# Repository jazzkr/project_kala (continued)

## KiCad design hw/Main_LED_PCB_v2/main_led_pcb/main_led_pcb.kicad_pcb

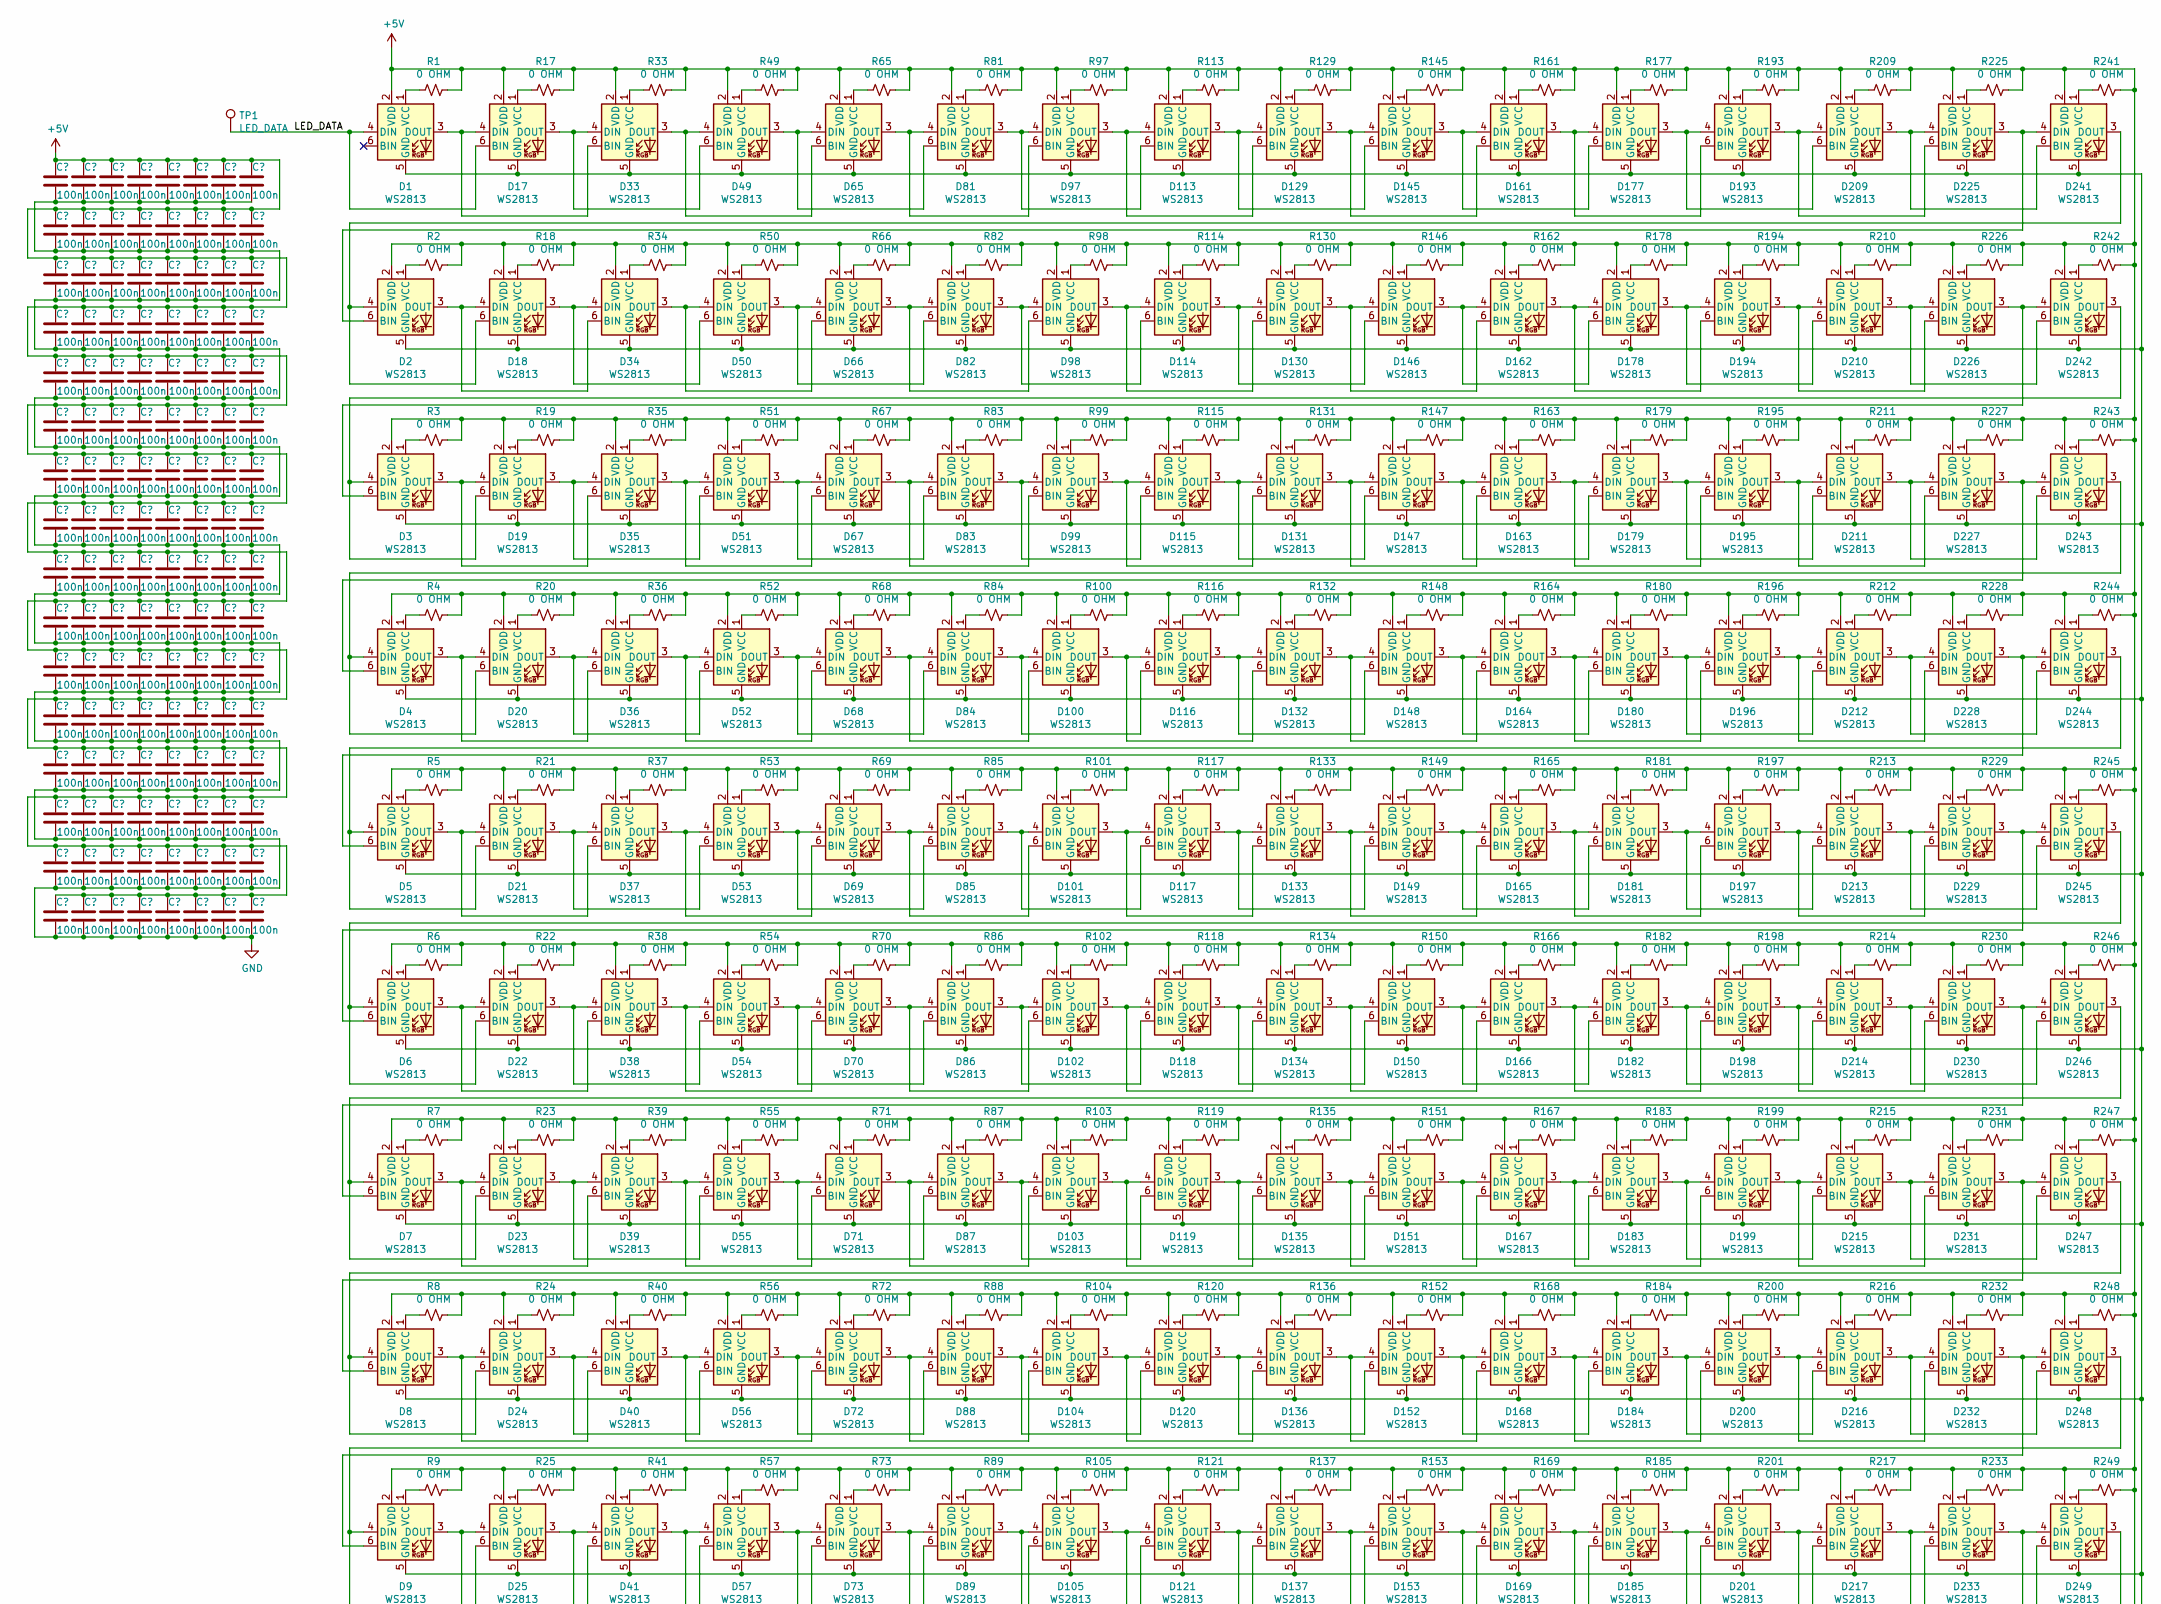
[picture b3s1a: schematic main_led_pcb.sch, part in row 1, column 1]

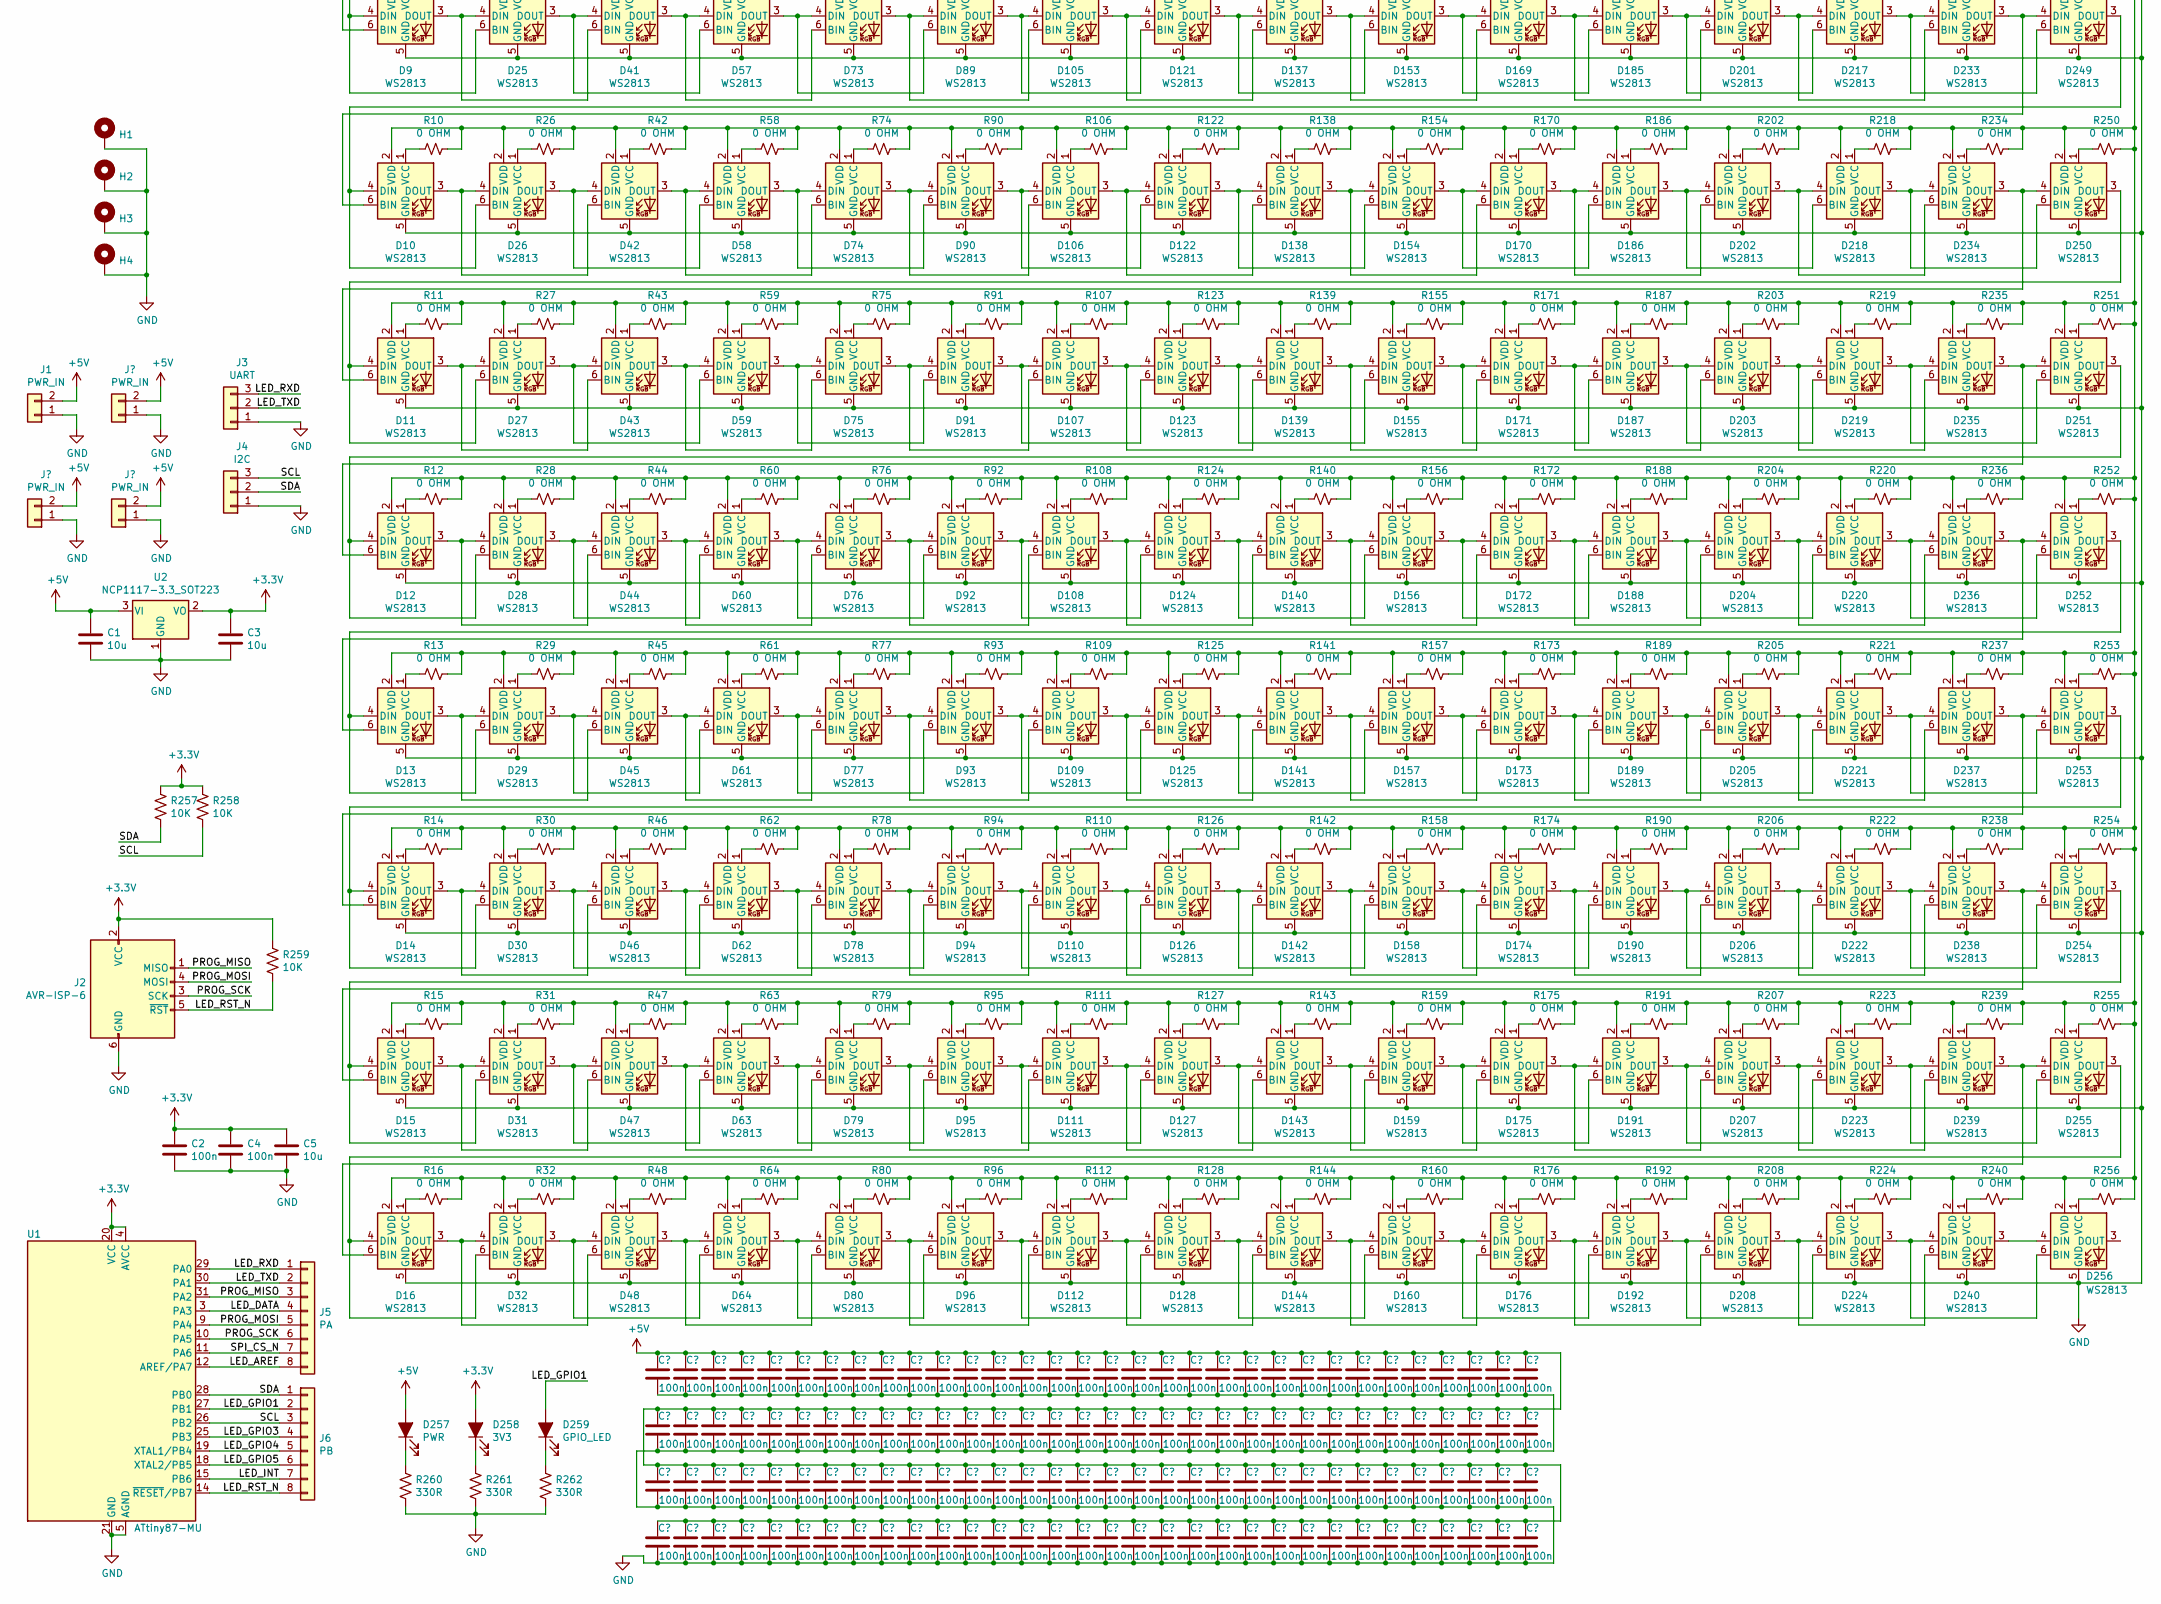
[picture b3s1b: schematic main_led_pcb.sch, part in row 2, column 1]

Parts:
C1, C3, C5: 10u; C_0805_2012Metric_Pad1.15x1.40mm_HandSolder
C2, C4: 100n; C_0805_2012Metric_Pad1.15x1.40mm_HandSolder
D1, D2, D3, D4, D5, D6, D7, D8, D9, D10, D11, D12, D13, D14, D15, D16, D17, D18, D19, D20, D21, D22, D23, D24, D25, D26, D27, D28, D29, D30, D31, D32, D33, D34, D35, D36, D37, D38, D39, D40, D41, D42, D43, D44, D45, D46, D47, D48, D49, D50, D51, D52, D53, D54, D55, D56, D57, D58, D59, D60, D61, D62, D63, D64, D65, D66, D67, D68, D69, D70, D71, D72, D73, D74, D75, D76, D77, D78, D79, D80, D81, D82, D83, D84, D85, D86, D87, D88, D89, D90, D91, D92, D93, D94, D95, D96, D97, D98, D99, D100, D101, D102, D103, D104, D105, D106, D107, D108, D109, D110, D111, D112, D113, D114, D115, D116, D117, D118, D119, D120, D121, D122, D123, D124, D125, D126, D127, D128, D129, D130, D131, D132, D133, D134, D135, D136, D137, D138, D139, D140, D141, D142, D143, D144, D145, D146, D147, D148, D149, D150, D151, D152, D153, D154, D155, D156, D157, D158, D159, D160, D161, D162, D163, D164, D165, D166, D167, D168, D169, D170, D171, D172, D173, D174, D175, D176, D177, D178, D179, D180, D181, D182, D183, D184, D185, D186, D187, D188, D189, D190, D191, D192, D193, D194, D195, D196, D197, D198, D199, D200, D201, D202, D203, D204, D205, D206, D207, D208, D209, D210, D211, D212, D213, D214, D215, D216, D217, D218, D219, D220, D221, D222, D223, D224, D225, D226, D227, D228, D229, D230, D231, D232, D233, D234, D235, D236, D237, D238, D239, D240, D241, D242, D243, D244, D245, D246, D247, D248, D249, D250, D251, D252, D253, D254, D255, D256: WS2813; LED_WS2812_PLCC6_5.0x5.0mm_P1.6mm
D257: PWR; LED_1206_3216Metric_Pad1.42x1.75mm_HandSolder
D258: 3V3; LED_1206_3216Metric_Pad1.42x1.75mm_HandSolder
D259: GPIO_LED; LED_1206_3216Metric_Pad1.42x1.75mm_HandSolder
H1: 1; MountingHole_2.2mm_M2_ISO7380_Pad
H2: 2; MountingHole_2.2mm_M2_ISO7380_Pad
H3: 3; MountingHole_2.2mm_M2_ISO7380_Pad
H4: 4; MountingHole_2.2mm_M2_ISO7380_Pad
J1: PWR_IN; PinHeader_1x02_P2.54mm_Vertical
J2: AVR-ISP-6; PinHeader_2x03_P2.54mm_Vertical_SMD
J3: UART; PinHeader_1x03_P2.54mm_Vertical
J4: I2C; PinHeader_1x03_P2.54mm_Vertical
J5: PA; PinHeader_1x08_P2.54mm_Vertical
J6: PB; PinHeader_1x08_P2.54mm_Vertical
R1, R2, R3, R4, R5, R6, R7, R8, R9, R10, R11, R12, R13, R14, R15, R16, R17, R18, R19, R20, R21, R22, R23, R24, R25, R26, R27, R28, R29, R30, R31, R32, R33, R34, R35, R36, R37, R38, R39, R40, R41, R42, R43, R44, R45, R46, R47, R48, R49, R50, R51, R52, R53, R54, R55, R56, R57, R58, R59, R60, R61, R62, R63, R64, R65, R66, R67, R68, R69, R70, R71, R72, R73, R74, R75, R76, R77, R78, R79, R80, R81, R82, R83, R84, R85, R86, R87, R88, R89, R90, R91, R92, R93, R94, R95, R96, R97, R98, R99, R100, R101, R102, R103, R104, R105, R106, R107, R108, R109, R110, R111, R112, R113, R114, R115, R116, R117, R118, R119, R120, R121, R122, R123, R124, R125, R126, R127, R128, R129, R130, R131, R132, R133, R134, R135, R136, R137, R138, R139, R140, R141, R142, R143, R144, R145, R146, R147, R148, R149, R150, R151, R152, R153, R154, R155, R156, R157, R158, R159, R160, R161, R162, R163, R164, R165, R166, R167, R168, R169, R170, R171, R172, R173, R174, R175, R176, R177, R178, R179, R180, R181, R182, R183, R184, R185, R186, R187, R188, R189, R190, R191, R192, R193, R194, R195, R196, R197, R198, R199, R200, R201, R202, R203, R204, R205, R206, R207, R208, R209, R210, R211, R212, R213, R214, R215, R216, R217, R218, R219, R220, R221, R222, R223, R224, R225, R226, R227, R228, R229, R230, R231, R232, R233, R234, R235, R236, R237, R238, R239, R240, R241, R242, R243, R244, R245, R246, R247, R248, R249, R250, R251, R252, R253, R254, R255, R256: 0 OHM; R_0805_2012Metric_Pad1.15x1.40mm_HandSolder
R257, R258, R259: 10K; R_0805_2012Metric_Pad1.15x1.40mm_HandSolder
R260, R261, R262: 330R; R_0805_2012Metric_Pad1.15x1.40mm_HandSolder
TP1: LED_DATA; TestPoint_Pad_D2.0mm
U1: ATtiny87-MU; QFN-32-1EP_5x5mm_P0.5mm_EP3.1x3.1mm
U2: NCP1117-3.3_SOT223; SOT-223-3_TabPin2

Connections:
+3V3: C2.1, C3.1, C4.1, C5.1, D258.2 (A), J2.2 (VCC), R257.1, R258.1, R259.1, U1.4 (AVCC), U1.20 (VCC), U2.2 (VO)
+5V: C1.1, D1.2 (VDD), D2.2 (VDD), D3.2 (VDD), D4.2 (VDD), D5.2 (VDD), D6.2 (VDD), D7.2 (VDD), D8.2 (VDD), D9.2 (VDD), D10.2 (VDD), D11.2 (VDD), D12.2 (VDD), D13.2 (VDD), D14.2 (VDD), D15.2 (VDD), D16.2 (VDD), D17.2 (VDD), D18.2 (VDD), D19.2 (VDD), D20.2 (VDD), D21.2 (VDD), D22.2 (VDD), D23.2 (VDD), D24.2 (VDD), D25.2 (VDD), D26.2 (VDD), D27.2 (VDD), D28.2 (VDD), D29.2 (VDD), D30.2 (VDD), D31.2 (VDD), D32.2 (VDD), D33.2 (VDD), D34.2 (VDD), D35.2 (VDD), D36.2 (VDD), D37.2 (VDD), D38.2 (VDD), D39.2 (VDD), D40.2 (VDD), D41.2 (VDD), D42.2 (VDD), D43.2 (VDD), D44.2 (VDD), D45.2 (VDD), D46.2 (VDD), D47.2 (VDD), D48.2 (VDD), D49.2 (VDD), D50.2 (VDD), D51.2 (VDD), D52.2 (VDD), D53.2 (VDD), D54.2 (VDD), D55.2 (VDD), D56.2 (VDD), D57.2 (VDD), D58.2 (VDD), D59.2 (VDD), D60.2 (VDD), D61.2 (VDD), D62.2 (VDD), D63.2 (VDD), D64.2 (VDD), D65.2 (VDD), D66.2 (VDD), D67.2 (VDD), D68.2 (VDD), D69.2 (VDD), D70.2 (VDD), D71.2 (VDD), D72.2 (VDD), D73.2 (VDD), D74.2 (VDD), D75.2 (VDD), D76.2 (VDD), D77.2 (VDD), D78.2 (VDD), D79.2 (VDD), D80.2 (VDD), D81.2 (VDD), D82.2 (VDD), D83.2 (VDD), D84.2 (VDD), D85.2 (VDD), D86.2 (VDD), D87.2 (VDD), D88.2 (VDD), D89.2 (VDD), D90.2 (VDD), D91.2 (VDD), D92.2 (VDD), D93.2 (VDD), D94.2 (VDD), D95.2 (VDD), D96.2 (VDD), D97.2 (VDD), D98.2 (VDD), D99.2 (VDD), D100.2 (VDD), D101.2 (VDD), D102.2 (VDD), D103.2 (VDD), D104.2 (VDD), D105.2 (VDD), D106.2 (VDD), D107.2 (VDD), D108.2 (VDD), D109.2 (VDD), D110.2 (VDD), D111.2 (VDD), D112.2 (VDD), D113.2 (VDD), D114.2 (VDD), D115.2 (VDD), D116.2 (VDD), D117.2 (VDD), D118.2 (VDD), D119.2 (VDD), D120.2 (VDD), D121.2 (VDD), D122.2 (VDD), D123.2 (VDD), D124.2 (VDD), D125.2 (VDD), D126.2 (VDD), D127.2 (VDD), D128.2 (VDD), D129.2 (VDD), D130.2 (VDD), D131.2 (VDD), D132.2 (VDD), D133.2 (VDD), D134.2 (VDD), D135.2 (VDD), D136.2 (VDD), D137.2 (VDD), D138.2 (VDD), D139.2 (VDD), D140.2 (VDD), D141.2 (VDD), D142.2 (VDD), D143.2 (VDD), D144.2 (VDD), D145.2 (VDD), D146.2 (VDD), D147.2 (VDD), D148.2 (VDD), D149.2 (VDD), D150.2 (VDD), D151.2 (VDD), D152.2 (VDD), D153.2 (VDD), D154.2 (VDD), D155.2 (VDD), D156.2 (VDD), D157.2 (VDD), D158.2 (VDD), D159.2 (VDD), D160.2 (VDD), D161.2 (VDD), D162.2 (VDD), D163.2 (VDD), D164.2 (VDD), D165.2 (VDD), D166.2 (VDD), D167.2 (VDD), D168.2 (VDD), D169.2 (VDD), D170.2 (VDD), D171.2 (VDD), D172.2 (VDD), D173.2 (VDD), D174.2 (VDD), D175.2 (VDD), D176.2 (VDD), D177.2 (VDD), D178.2 (VDD), D179.2 (VDD), D180.2 (VDD), D181.2 (VDD), D182.2 (VDD), D183.2 (VDD), D184.2 (VDD), D185.2 (VDD), D186.2 (VDD), D187.2 (VDD), D188.2 (VDD), D189.2 (VDD), D190.2 (VDD), D191.2 (VDD), D192.2 (VDD), D193.2 (VDD), D194.2 (VDD), D195.2 (VDD), D196.2 (VDD), D197.2 (VDD), D198.2 (VDD), D199.2 (VDD), D200.2 (VDD), D201.2 (VDD), D202.2 (VDD), D203.2 (VDD), D204.2 (VDD), D205.2 (VDD), D206.2 (VDD), D207.2 (VDD), D208.2 (VDD), D209.2 (VDD), D210.2 (VDD), D211.2 (VDD), D212.2 (VDD), D213.2 (VDD), D214.2 (VDD), D215.2 (VDD), D216.2 (VDD), D217.2 (VDD), D218.2 (VDD), D219.2 (VDD), D220.2 (VDD), D221.2 (VDD), D222.2 (VDD), D223.2 (VDD), D224.2 (VDD), D225.2 (VDD), D226.2 (VDD), D227.2 (VDD), D228.2 (VDD), D229.2 (VDD), D230.2 (VDD), D231.2 (VDD), D232.2 (VDD), D233.2 (VDD), D234.2 (VDD), D235.2 (VDD), D236.2 (VDD), D237.2 (VDD), D238.2 (VDD), D239.2 (VDD), D240.2 (VDD), D241.2 (VDD), D242.2 (VDD), D243.2 (VDD), D244.2 (VDD), D245.2 (VDD), D246.2 (VDD), D247.2 (VDD), D248.2 (VDD), D249.2 (VDD), D250.2 (VDD), D251.2 (VDD), D252.2 (VDD), D253.2 (VDD), D254.2 (VDD), D255.2 (VDD), D256.2 (VDD), D257.2 (A), J1.2, R1.1, R2.1, R3.1, R4.1, R5.1, R6.1, R7.1, R8.1, R9.1, R10.1, R11.1, R12.1, R13.1, R14.1, R15.1, R16.1, R17.1, R18.1, R19.1, R20.1, R21.1, R22.1, R23.1, R24.1, R25.1, R26.1, R27.1, R28.1, R29.1, R30.1, R31.1, R32.1, R33.1, R34.1, R35.1, R36.1, R37.1, R38.1, R39.1, R40.1, R41.1, R42.1, R43.1, R44.1, R45.1, R46.1, R47.1, R48.1, R49.1, R50.1, R51.1, R52.1, R53.1, R54.1, R55.1, R56.1, R57.1, R58.1, R59.1, R60.1, R61.1, R62.1, R63.1, R64.1, R65.1, R66.1, R67.1, R68.1, R69.1, R70.1, R71.1, R72.1, R73.1, R74.1, R75.1, R76.1, R77.1, R78.1, R79.1, R80.1, R81.1, R82.1, R83.1, R84.1, R85.1, R86.1, R87.1, R88.1, R89.1, R90.1, R91.1, R92.1, R93.1, R94.1, R95.1, R96.1, R97.1, R98.1, R99.1, R100.1, R101.1, R102.1, R103.1, R104.1, R105.1, R106.1, R107.1, R108.1, R109.1, R110.1, R111.1, R112.1, R113.1, R114.1, R115.1, R116.1, R117.1, R118.1, R119.1, R120.1, R121.1, R122.1, R123.1, R124.1, R125.1, R126.1, R127.1, R128.1, R129.1, R130.1, R131.1, R132.1, R133.1, R134.1, R135.1, R136.1, R137.1, R138.1, R139.1, R140.1, R141.1, R142.1, R143.1, R144.1, R145.1, R146.1, R147.1, R148.1, R149.1, R150.1, R151.1, R152.1, R153.1, R154.1, R155.1, R156.1, R157.1, R158.1, R159.1, R160.1, R161.1, R162.1, R163.1, R164.1, R165.1, R166.1, R167.1, R168.1, R169.1, R170.1, R171.1, R172.1, R173.1, R174.1, R175.1, R176.1, R177.1, R178.1, R179.1, R180.1, R181.1, R182.1, R183.1, R184.1, R185.1, R186.1, R187.1, R188.1, R189.1, R190.1, R191.1, R192.1, R193.1, R194.1, R195.1, R196.1, R197.1, R198.1, R199.1, R200.1, R201.1, R202.1, R203.1, R204.1, R205.1, R206.1, R207.1, R208.1, R209.1, R210.1, R211.1, R212.1, R213.1, R214.1, R215.1, R216.1, R217.1, R218.1, R219.1, R220.1, R221.1, R222.1, R223.1, R224.1, R225.1, R226.1, R227.1, R228.1, R229.1, R230.1, R231.1, R232.1, R233.1, R234.1, R235.1, R236.1, R237.1, R238.1, R239.1, R240.1, R241.1, R242.1, R243.1, R244.1, R245.1, R246.1, R247.1, R248.1, R249.1, R250.1, R251.1, R252.1, R253.1, R254.1, R255.1, R256.1, U2.3 (VI)
/LED_AREF: J5.8, U1.12 (AREF/PA7)
/LED_DATA: D1.4 (DIN), D17.6 (BIN), J5.4, TP1.1, U1.3 (PA3)
/LED_GPIO1: D259.2 (A), J6.2, U1.27 (PB1)
/LED_GPIO3: J6.4, U1.25 (PB3)
/LED_GPIO4: J6.5, U1.19 (XTAL1/PB4)
/LED_GPIO5: J6.6, U1.18 (XTAL2/PB5)
/LED_INT: J6.7, U1.15 (PB6)
/LED_RST_N: J2.5 (~RST), J6.8, R259.2, U1.14 (~RESET~/PB7)
/PROG_MISO: J2.1 (MISO), J5.3, U1.31 (PA2)
/PROG_MOSI: J2.4 (MOSI), J5.5, U1.9 (PA4)
/PROG_SCK: J2.3 (SCK), J5.6, U1.10 (PA5)
/SPI_CS_N: J5.7, U1.11 (PA6)
unnamed: D1.1 (VCC), R1.2
unnamed: D1.3 (DOUT), D17.4 (DIN), D33.6 (BIN)
unnamed: D2.1 (VCC), R2.2
unnamed: D2.6 (BIN), D225.3 (DOUT), D241.4 (DIN)
unnamed: D3.1 (VCC), R3.2
unnamed: D4.1 (VCC), R4.2
unnamed: D5.1 (VCC), R5.2
unnamed: D6.1 (VCC), R6.2
unnamed: D7.1 (VCC), R7.2
unnamed: D8.1 (VCC), R8.2
unnamed: D9.1 (VCC), R9.2
unnamed: D10.1 (VCC), R10.2
unnamed: D10.3 (DOUT), D26.4 (DIN), D42.6 (BIN)
unnamed: D10.4 (DIN), D26.6 (BIN), D249.3 (DOUT)
unnamed: D10.6 (BIN), D233.3 (DOUT), D249.4 (DIN)
unnamed: D11.1 (VCC), R11.2
unnamed: D11.3 (DOUT), D27.4 (DIN), D43.6 (BIN)
unnamed: D11.4 (DIN), D27.6 (BIN), D250.3 (DOUT)
unnamed: D11.6 (BIN), D234.3 (DOUT), D250.4 (DIN)
unnamed: D12.1 (VCC), R12.2
unnamed: D12.3 (DOUT), D28.4 (DIN), D44.6 (BIN)
unnamed: D12.4 (DIN), D28.6 (BIN), D251.3 (DOUT)
unnamed: D12.6 (BIN), D235.3 (DOUT), D251.4 (DIN)
unnamed: D13.1 (VCC), R13.2
unnamed: D13.3 (DOUT), D29.4 (DIN), D45.6 (BIN)
unnamed: D13.4 (DIN), D29.6 (BIN), D252.3 (DOUT)
unnamed: D13.6 (BIN), D236.3 (DOUT), D252.4 (DIN)
unnamed: D14.1 (VCC), R14.2
unnamed: D14.3 (DOUT), D30.4 (DIN), D46.6 (BIN)
unnamed: D14.4 (DIN), D30.6 (BIN), D253.3 (DOUT)
unnamed: D14.6 (BIN), D237.3 (DOUT), D253.4 (DIN)
unnamed: D15.1 (VCC), R15.2
unnamed: D15.3 (DOUT), D31.4 (DIN), D47.6 (BIN)
unnamed: D15.4 (DIN), D31.6 (BIN), D254.3 (DOUT)
unnamed: D15.6 (BIN), D238.3 (DOUT), D254.4 (DIN)
unnamed: D16.1 (VCC), R16.2
unnamed: D16.3 (DOUT), D32.4 (DIN), D48.6 (BIN)
unnamed: D16.4 (DIN), D32.6 (BIN), D255.3 (DOUT)
unnamed: D16.6 (BIN), D239.3 (DOUT), D255.4 (DIN)
unnamed: D17.1 (VCC), R17.2
unnamed: D17.3 (DOUT), D33.4 (DIN), D49.6 (BIN)
unnamed: D18.1 (VCC), R18.2
unnamed: D18.3 (DOUT), D34.4 (DIN), D50.6 (BIN)
unnamed: D2.3 (DOUT), D18.4 (DIN), D34.6 (BIN)
unnamed: D2.4 (DIN), D18.6 (BIN), D241.3 (DOUT)
unnamed: D19.1 (VCC), R19.2
unnamed: D19.3 (DOUT), D35.4 (DIN), D51.6 (BIN)
unnamed: D3.3 (DOUT), D19.4 (DIN), D35.6 (BIN)
unnamed: D3.4 (DIN), D19.6 (BIN), D242.3 (DOUT)
unnamed: D20.1 (VCC), R20.2
unnamed: D20.3 (DOUT), D36.4 (DIN), D52.6 (BIN)
unnamed: D4.3 (DOUT), D20.4 (DIN), D36.6 (BIN)
unnamed: D4.4 (DIN), D20.6 (BIN), D243.3 (DOUT)
unnamed: D21.1 (VCC), R21.2
unnamed: D21.3 (DOUT), D37.4 (DIN), D53.6 (BIN)
unnamed: D5.3 (DOUT), D21.4 (DIN), D37.6 (BIN)
unnamed: D5.4 (DIN), D21.6 (BIN), D244.3 (DOUT)
unnamed: D22.1 (VCC), R22.2
unnamed: D22.3 (DOUT), D38.4 (DIN), D54.6 (BIN)
unnamed: D6.3 (DOUT), D22.4 (DIN), D38.6 (BIN)
unnamed: D6.4 (DIN), D22.6 (BIN), D245.3 (DOUT)
unnamed: D23.1 (VCC), R23.2
unnamed: D23.3 (DOUT), D39.4 (DIN), D55.6 (BIN)
unnamed: D7.3 (DOUT), D23.4 (DIN), D39.6 (BIN)
unnamed: D7.4 (DIN), D23.6 (BIN), D246.3 (DOUT)
unnamed: D24.1 (VCC), R24.2
unnamed: D24.3 (DOUT), D40.4 (DIN), D56.6 (BIN)
unnamed: D8.3 (DOUT), D24.4 (DIN), D40.6 (BIN)
unnamed: D8.4 (DIN), D24.6 (BIN), D247.3 (DOUT)
unnamed: D25.1 (VCC), R25.2
unnamed: D25.3 (DOUT), D41.4 (DIN), D57.6 (BIN)
unnamed: D9.3 (DOUT), D25.4 (DIN), D41.6 (BIN)
unnamed: D26.1 (VCC), R26.2
unnamed: D26.3 (DOUT), D42.4 (DIN), D58.6 (BIN)
unnamed: D27.1 (VCC), R27.2
unnamed: D27.3 (DOUT), D43.4 (DIN), D59.6 (BIN)
unnamed: D28.1 (VCC), R28.2
unnamed: D28.3 (DOUT), D44.4 (DIN), D60.6 (BIN)
unnamed: D29.1 (VCC), R29.2
unnamed: D29.3 (DOUT), D45.4 (DIN), D61.6 (BIN)
unnamed: D30.1 (VCC), R30.2
unnamed: D30.3 (DOUT), D46.4 (DIN), D62.6 (BIN)
unnamed: D31.1 (VCC), R31.2
unnamed: D31.3 (DOUT), D47.4 (DIN), D63.6 (BIN)
unnamed: D32.1 (VCC), R32.2
unnamed: D32.3 (DOUT), D48.4 (DIN), D64.6 (BIN)
unnamed: D33.1 (VCC), R33.2
unnamed: D33.3 (DOUT), D49.4 (DIN), D65.6 (BIN)
unnamed: D34.1 (VCC), R34.2
unnamed: D34.3 (DOUT), D50.4 (DIN), D66.6 (BIN)
unnamed: D35.1 (VCC), R35.2
unnamed: D35.3 (DOUT), D51.4 (DIN), D67.6 (BIN)
unnamed: D36.1 (VCC), R36.2
unnamed: D36.3 (DOUT), D52.4 (DIN), D68.6 (BIN)
unnamed: D37.1 (VCC), R37.2
unnamed: D37.3 (DOUT), D53.4 (DIN), D69.6 (BIN)
unnamed: D38.1 (VCC), R38.2
unnamed: D38.3 (DOUT), D54.4 (DIN), D70.6 (BIN)
unnamed: D39.1 (VCC), R39.2
unnamed: D39.3 (DOUT), D55.4 (DIN), D71.6 (BIN)
unnamed: D40.1 (VCC), R40.2
unnamed: D40.3 (DOUT), D56.4 (DIN), D72.6 (BIN)
unnamed: D41.1 (VCC), R41.2
unnamed: D41.3 (DOUT), D57.4 (DIN), D73.6 (BIN)
unnamed: D42.1 (VCC), R42.2
unnamed: D42.3 (DOUT), D58.4 (DIN), D74.6 (BIN)
unnamed: D43.1 (VCC), R43.2
unnamed: D43.3 (DOUT), D59.4 (DIN), D75.6 (BIN)
unnamed: D44.1 (VCC), R44.2
unnamed: D44.3 (DOUT), D60.4 (DIN), D76.6 (BIN)
unnamed: D45.1 (VCC), R45.2
unnamed: D45.3 (DOUT), D61.4 (DIN), D77.6 (BIN)
unnamed: D46.1 (VCC), R46.2
unnamed: D46.3 (DOUT), D62.4 (DIN), D78.6 (BIN)
unnamed: D47.1 (VCC), R47.2
unnamed: D47.3 (DOUT), D63.4 (DIN), D79.6 (BIN)
unnamed: D48.1 (VCC), R48.2
unnamed: D48.3 (DOUT), D64.4 (DIN), D80.6 (BIN)
unnamed: D49.1 (VCC), R49.2
unnamed: D49.3 (DOUT), D65.4 (DIN), D81.6 (BIN)
unnamed: D50.1 (VCC), R50.2
unnamed: D50.3 (DOUT), D66.4 (DIN), D82.6 (BIN)
unnamed: D51.1 (VCC), R51.2
unnamed: D51.3 (DOUT), D67.4 (DIN), D83.6 (BIN)
unnamed: D52.1 (VCC), R52.2
unnamed: D52.3 (DOUT), D68.4 (DIN), D84.6 (BIN)
unnamed: D53.1 (VCC), R53.2
unnamed: D53.3 (DOUT), D69.4 (DIN), D85.6 (BIN)
unnamed: D54.1 (VCC), R54.2
unnamed: D54.3 (DOUT), D70.4 (DIN), D86.6 (BIN)
unnamed: D55.1 (VCC), R55.2
unnamed: D55.3 (DOUT), D71.4 (DIN), D87.6 (BIN)
unnamed: D56.1 (VCC), R56.2
unnamed: D56.3 (DOUT), D72.4 (DIN), D88.6 (BIN)
unnamed: D57.1 (VCC), R57.2
unnamed: D57.3 (DOUT), D73.4 (DIN), D89.6 (BIN)
unnamed: D58.1 (VCC), R58.2
unnamed: D58.3 (DOUT), D74.4 (DIN), D90.6 (BIN)
unnamed: D59.1 (VCC), R59.2
unnamed: D59.3 (DOUT), D75.4 (DIN), D91.6 (BIN)
unnamed: D60.1 (VCC), R60.2
unnamed: D60.3 (DOUT), D76.4 (DIN), D92.6 (BIN)
unnamed: D61.1 (VCC), R61.2
unnamed: D61.3 (DOUT), D77.4 (DIN), D93.6 (BIN)
unnamed: D62.1 (VCC), R62.2
unnamed: D62.3 (DOUT), D78.4 (DIN), D94.6 (BIN)
unnamed: D63.1 (VCC), R63.2
unnamed: D63.3 (DOUT), D79.4 (DIN), D95.6 (BIN)
unnamed: D64.1 (VCC), R64.2
unnamed: D64.3 (DOUT), D80.4 (DIN), D96.6 (BIN)
unnamed: D65.1 (VCC), R65.2
unnamed: D65.3 (DOUT), D81.4 (DIN), D97.6 (BIN)
unnamed: D66.1 (VCC), R66.2
unnamed: D66.3 (DOUT), D82.4 (DIN), D98.6 (BIN)
unnamed: D67.1 (VCC), R67.2
unnamed: D67.3 (DOUT), D83.4 (DIN), D99.6 (BIN)
unnamed: D68.1 (VCC), R68.2
unnamed: D69.1 (VCC), R69.2
unnamed: D70.1 (VCC), R70.2
unnamed: D71.1 (VCC), R71.2
unnamed: D72.1 (VCC), R72.2
unnamed: D73.1 (VCC), R73.2
unnamed: D74.1 (VCC), R74.2
unnamed: D75.1 (VCC), R75.2
unnamed: D76.1 (VCC), R76.2
unnamed: D77.1 (VCC), R77.2
unnamed: D78.1 (VCC), R78.2
unnamed: D79.1 (VCC), R79.2
unnamed: D80.1 (VCC), R80.2
unnamed: D81.1 (VCC), R81.2
unnamed: D82.1 (VCC), R82.2
unnamed: D83.1 (VCC), R83.2
unnamed: D84.1 (VCC), R84.2
unnamed: D85.1 (VCC), R85.2
unnamed: D86.1 (VCC), R86.2
unnamed: D87.1 (VCC), R87.2
unnamed: D88.1 (VCC), R88.2
unnamed: D89.1 (VCC), R89.2
unnamed: D90.1 (VCC), R90.2
unnamed: D91.1 (VCC), R91.2
unnamed: D92.1 (VCC), R92.2
unnamed: D93.1 (VCC), R93.2
unnamed: D94.1 (VCC), R94.2
unnamed: D95.1 (VCC), R95.2
unnamed: D96.1 (VCC), R96.2
unnamed: D97.1 (VCC), R97.2
unnamed: D98.1 (VCC), R98.2
unnamed: D99.1 (VCC), R99.2
unnamed: D100.1 (VCC), R100.2
unnamed: D100.3 (DOUT), D116.4 (DIN), D132.6 (BIN)
unnamed: D84.3 (DOUT), D100.4 (DIN), D116.6 (BIN)
unnamed: D68.3 (DOUT), D84.4 (DIN), D100.6 (BIN)
unnamed: D101.1 (VCC), R101.2
unnamed: D101.3 (DOUT), D117.4 (DIN), D133.6 (BIN)
unnamed: D85.3 (DOUT), D101.4 (DIN), D117.6 (BIN)
unnamed: D69.3 (DOUT), D85.4 (DIN), D101.6 (BIN)
unnamed: D102.1 (VCC), R102.2
unnamed: D102.3 (DOUT), D118.4 (DIN), D134.6 (BIN)
unnamed: D86.3 (DOUT), D102.4 (DIN), D118.6 (BIN)
unnamed: D70.3 (DOUT), D86.4 (DIN), D102.6 (BIN)
unnamed: D103.1 (VCC), R103.2
unnamed: D103.3 (DOUT), D119.4 (DIN), D135.6 (BIN)
unnamed: D87.3 (DOUT), D103.4 (DIN), D119.6 (BIN)
unnamed: D71.3 (DOUT), D87.4 (DIN), D103.6 (BIN)
unnamed: D104.1 (VCC), R104.2
unnamed: D104.3 (DOUT), D120.4 (DIN), D136.6 (BIN)
unnamed: D88.3 (DOUT), D104.4 (DIN), D120.6 (BIN)
unnamed: D72.3 (DOUT), D88.4 (DIN), D104.6 (BIN)
unnamed: D105.1 (VCC), R105.2
unnamed: D105.3 (DOUT), D121.4 (DIN), D137.6 (BIN)
unnamed: D89.3 (DOUT), D105.4 (DIN), D121.6 (BIN)
unnamed: D73.3 (DOUT), D89.4 (DIN), D105.6 (BIN)
unnamed: D106.1 (VCC), R106.2
unnamed: D106.3 (DOUT), D122.4 (DIN), D138.6 (BIN)
unnamed: D90.3 (DOUT), D106.4 (DIN), D122.6 (BIN)
unnamed: D74.3 (DOUT), D90.4 (DIN), D106.6 (BIN)
unnamed: D107.1 (VCC), R107.2
unnamed: D107.3 (DOUT), D123.4 (DIN), D139.6 (BIN)
unnamed: D91.3 (DOUT), D107.4 (DIN), D123.6 (BIN)
unnamed: D75.3 (DOUT), D91.4 (DIN), D107.6 (BIN)
unnamed: D108.1 (VCC), R108.2
unnamed: D108.3 (DOUT), D124.4 (DIN), D140.6 (BIN)
unnamed: D92.3 (DOUT), D108.4 (DIN), D124.6 (BIN)
unnamed: D76.3 (DOUT), D92.4 (DIN), D108.6 (BIN)
unnamed: D109.1 (VCC), R109.2
unnamed: D109.3 (DOUT), D125.4 (DIN), D141.6 (BIN)
unnamed: D93.3 (DOUT), D109.4 (DIN), D125.6 (BIN)
unnamed: D77.3 (DOUT), D93.4 (DIN), D109.6 (BIN)
unnamed: D110.1 (VCC), R110.2
unnamed: D110.3 (DOUT), D126.4 (DIN), D142.6 (BIN)
unnamed: D94.3 (DOUT), D110.4 (DIN), D126.6 (BIN)
unnamed: D78.3 (DOUT), D94.4 (DIN), D110.6 (BIN)
unnamed: D111.1 (VCC), R111.2
unnamed: D111.3 (DOUT), D127.4 (DIN), D143.6 (BIN)
unnamed: D95.3 (DOUT), D111.4 (DIN), D127.6 (BIN)
unnamed: D79.3 (DOUT), D95.4 (DIN), D111.6 (BIN)
unnamed: D112.1 (VCC), R112.2
unnamed: D112.3 (DOUT), D128.4 (DIN), D144.6 (BIN)
unnamed: D96.3 (DOUT), D112.4 (DIN), D128.6 (BIN)
unnamed: D80.3 (DOUT), D96.4 (DIN), D112.6 (BIN)
unnamed: D113.1 (VCC), R113.2
unnamed: D113.3 (DOUT), D129.4 (DIN), D145.6 (BIN)
unnamed: D97.3 (DOUT), D113.4 (DIN), D129.6 (BIN)
unnamed: D81.3 (DOUT), D97.4 (DIN), D113.6 (BIN)
unnamed: D114.1 (VCC), R114.2
unnamed: D114.3 (DOUT), D130.4 (DIN), D146.6 (BIN)
unnamed: D98.3 (DOUT), D114.4 (DIN), D130.6 (BIN)
unnamed: D82.3 (DOUT), D98.4 (DIN), D114.6 (BIN)
unnamed: D115.1 (VCC), R115.2
unnamed: D115.3 (DOUT), D131.4 (DIN), D147.6 (BIN)
unnamed: D99.3 (DOUT), D115.4 (DIN), D131.6 (BIN)
unnamed: D83.3 (DOUT), D99.4 (DIN), D115.6 (BIN)
unnamed: D116.1 (VCC), R116.2
unnamed: D116.3 (DOUT), D132.4 (DIN), D148.6 (BIN)
unnamed: D117.1 (VCC), R117.2
unnamed: D117.3 (DOUT), D133.4 (DIN), D149.6 (BIN)
unnamed: D118.1 (VCC), R118.2
unnamed: D118.3 (DOUT), D134.4 (DIN), D150.6 (BIN)
unnamed: D119.1 (VCC), R119.2
unnamed: D119.3 (DOUT), D135.4 (DIN), D151.6 (BIN)
unnamed: D120.1 (VCC), R120.2
unnamed: D120.3 (DOUT), D136.4 (DIN), D152.6 (BIN)
unnamed: D121.1 (VCC), R121.2
unnamed: D121.3 (DOUT), D137.4 (DIN), D153.6 (BIN)
unnamed: D122.1 (VCC), R122.2
unnamed: D122.3 (DOUT), D138.4 (DIN), D154.6 (BIN)
unnamed: D123.1 (VCC), R123.2
unnamed: D123.3 (DOUT), D139.4 (DIN), D155.6 (BIN)
unnamed: D124.1 (VCC), R124.2
unnamed: D124.3 (DOUT), D140.4 (DIN), D156.6 (BIN)
unnamed: D125.1 (VCC), R125.2
unnamed: D125.3 (DOUT), D141.4 (DIN), D157.6 (BIN)
unnamed: D126.1 (VCC), R126.2
unnamed: D126.3 (DOUT), D142.4 (DIN), D158.6 (BIN)
unnamed: D127.1 (VCC), R127.2
unnamed: D127.3 (DOUT), D143.4 (DIN), D159.6 (BIN)
unnamed: D128.1 (VCC), R128.2
unnamed: D128.3 (DOUT), D144.4 (DIN), D160.6 (BIN)
unnamed: D129.1 (VCC), R129.2
unnamed: D129.3 (DOUT), D145.4 (DIN), D161.6 (BIN)
unnamed: D130.1 (VCC), R130.2
unnamed: D130.3 (DOUT), D146.4 (DIN), D162.6 (BIN)
unnamed: D131.1 (VCC), R131.2
unnamed: D131.3 (DOUT), D147.4 (DIN), D163.6 (BIN)
unnamed: D132.1 (VCC), R132.2
unnamed: D132.3 (DOUT), D148.4 (DIN), D164.6 (BIN)
unnamed: D133.1 (VCC), R133.2
unnamed: D133.3 (DOUT), D149.4 (DIN), D165.6 (BIN)
unnamed: D134.1 (VCC), R134.2
unnamed: D134.3 (DOUT), D150.4 (DIN), D166.6 (BIN)
unnamed: D135.1 (VCC), R135.2
unnamed: D135.3 (DOUT), D151.4 (DIN), D167.6 (BIN)
unnamed: D136.1 (VCC), R136.2
unnamed: D136.3 (DOUT), D152.4 (DIN), D168.6 (BIN)
unnamed: D137.1 (VCC), R137.2
unnamed: D137.3 (DOUT), D153.4 (DIN), D169.6 (BIN)
unnamed: D138.1 (VCC), R138.2
unnamed: D138.3 (DOUT), D154.4 (DIN), D170.6 (BIN)
unnamed: D139.1 (VCC), R139.2
unnamed: D139.3 (DOUT), D155.4 (DIN), D171.6 (BIN)
unnamed: D140.1 (VCC), R140.2
unnamed: D140.3 (DOUT), D156.4 (DIN), D172.6 (BIN)
unnamed: D141.1 (VCC), R141.2
unnamed: D141.3 (DOUT), D157.4 (DIN), D173.6 (BIN)
unnamed: D142.1 (VCC), R142.2
unnamed: D142.3 (DOUT), D158.4 (DIN), D174.6 (BIN)
unnamed: D143.1 (VCC), R143.2
unnamed: D143.3 (DOUT), D159.4 (DIN), D175.6 (BIN)
unnamed: D144.1 (VCC), R144.2
unnamed: D144.3 (DOUT), D160.4 (DIN), D176.6 (BIN)
unnamed: D145.1 (VCC), R145.2
unnamed: D145.3 (DOUT), D161.4 (DIN), D177.6 (BIN)
unnamed: D146.1 (VCC), R146.2
unnamed: D146.3 (DOUT), D162.4 (DIN), D178.6 (BIN)
unnamed: D147.1 (VCC), R147.2
unnamed: D147.3 (DOUT), D163.4 (DIN), D179.6 (BIN)
unnamed: D148.1 (VCC), R148.2
unnamed: D148.3 (DOUT), D164.4 (DIN), D180.6 (BIN)
unnamed: D149.1 (VCC), R149.2
unnamed: D149.3 (DOUT), D165.4 (DIN), D181.6 (BIN)
unnamed: D150.1 (VCC), R150.2
unnamed: D150.3 (DOUT), D166.4 (DIN), D182.6 (BIN)
unnamed: D151.1 (VCC), R151.2
unnamed: D151.3 (DOUT), D167.4 (DIN), D183.6 (BIN)
unnamed: D152.1 (VCC), R152.2
unnamed: D152.3 (DOUT), D168.4 (DIN), D184.6 (BIN)
unnamed: D153.1 (VCC), R153.2
unnamed: D153.3 (DOUT), D169.4 (DIN), D185.6 (BIN)
unnamed: D154.1 (VCC), R154.2
unnamed: D154.3 (DOUT), D170.4 (DIN), D186.6 (BIN)
unnamed: D155.1 (VCC), R155.2
unnamed: D155.3 (DOUT), D171.4 (DIN), D187.6 (BIN)
unnamed: D156.1 (VCC), R156.2
unnamed: D156.3 (DOUT), D172.4 (DIN), D188.6 (BIN)
unnamed: D157.1 (VCC), R157.2
unnamed: D157.3 (DOUT), D173.4 (DIN), D189.6 (BIN)
unnamed: D158.1 (VCC), R158.2
unnamed: D158.3 (DOUT), D174.4 (DIN), D190.6 (BIN)
unnamed: D159.1 (VCC), R159.2
unnamed: D159.3 (DOUT), D175.4 (DIN), D191.6 (BIN)
unnamed: D160.1 (VCC), R160.2
unnamed: D160.3 (DOUT), D176.4 (DIN), D192.6 (BIN)
unnamed: D161.1 (VCC), R161.2
unnamed: D161.3 (DOUT), D177.4 (DIN), D193.6 (BIN)
unnamed: D162.1 (VCC), R162.2
unnamed: D162.3 (DOUT), D178.4 (DIN), D194.6 (BIN)
unnamed: D163.1 (VCC), R163.2
unnamed: D163.3 (DOUT), D179.4 (DIN), D195.6 (BIN)
unnamed: D164.1 (VCC), R164.2
unnamed: D164.3 (DOUT), D180.4 (DIN), D196.6 (BIN)
unnamed: D165.1 (VCC), R165.2
unnamed: D165.3 (DOUT), D181.4 (DIN), D197.6 (BIN)
unnamed: D166.1 (VCC), R166.2
unnamed: D166.3 (DOUT), D182.4 (DIN), D198.6 (BIN)
unnamed: D167.1 (VCC), R167.2
unnamed: D167.3 (DOUT), D183.4 (DIN), D199.6 (BIN)
unnamed: D168.1 (VCC), R168.2
unnamed: D168.3 (DOUT), D184.4 (DIN), D200.6 (BIN)
unnamed: D169.1 (VCC), R169.2
unnamed: D169.3 (DOUT), D185.4 (DIN), D201.6 (BIN)
unnamed: D170.1 (VCC), R170.2
unnamed: D170.3 (DOUT), D186.4 (DIN), D202.6 (BIN)
unnamed: D171.1 (VCC), R171.2
unnamed: D171.3 (DOUT), D187.4 (DIN), D203.6 (BIN)
unnamed: D172.1 (VCC), R172.2
unnamed: D172.3 (DOUT), D188.4 (DIN), D204.6 (BIN)
unnamed: D173.1 (VCC), R173.2
unnamed: D173.3 (DOUT), D189.4 (DIN), D205.6 (BIN)
unnamed: D174.1 (VCC), R174.2
unnamed: D174.3 (DOUT), D190.4 (DIN), D206.6 (BIN)
unnamed: D175.1 (VCC), R175.2
unnamed: D175.3 (DOUT), D191.4 (DIN), D207.6 (BIN)
unnamed: D176.1 (VCC), R176.2
unnamed: D176.3 (DOUT), D192.4 (DIN), D208.6 (BIN)
unnamed: D177.1 (VCC), R177.2
unnamed: D177.3 (DOUT), D193.4 (DIN), D209.6 (BIN)
unnamed: D178.1 (VCC), R178.2
unnamed: D178.3 (DOUT), D194.4 (DIN), D210.6 (BIN)
unnamed: D179.1 (VCC), R179.2
unnamed: D179.3 (DOUT), D195.4 (DIN), D211.6 (BIN)
unnamed: D180.1 (VCC), R180.2
unnamed: D180.3 (DOUT), D196.4 (DIN), D212.6 (BIN)
unnamed: D181.1 (VCC), R181.2
unnamed: D181.3 (DOUT), D197.4 (DIN), D213.6 (BIN)
unnamed: D182.1 (VCC), R182.2
unnamed: D182.3 (DOUT), D198.4 (DIN), D214.6 (BIN)
unnamed: D183.1 (VCC), R183.2
unnamed: D183.3 (DOUT), D199.4 (DIN), D215.6 (BIN)
unnamed: D184.1 (VCC), R184.2
unnamed: D184.3 (DOUT), D200.4 (DIN), D216.6 (BIN)
unnamed: D185.1 (VCC), R185.2
unnamed: D185.3 (DOUT), D201.4 (DIN), D217.6 (BIN)
unnamed: D186.1 (VCC), R186.2
unnamed: D186.3 (DOUT), D202.4 (DIN), D218.6 (BIN)
unnamed: D187.1 (VCC), R187.2
unnamed: D187.3 (DOUT), D203.4 (DIN), D219.6 (BIN)
unnamed: D188.1 (VCC), R188.2
unnamed: D188.3 (DOUT), D204.4 (DIN), D220.6 (BIN)
unnamed: D189.1 (VCC), R189.2
unnamed: D189.3 (DOUT), D205.4 (DIN), D221.6 (BIN)
unnamed: D190.1 (VCC), R190.2
unnamed: D190.3 (DOUT), D206.4 (DIN), D222.6 (BIN)
unnamed: D191.1 (VCC), R191.2
unnamed: D191.3 (DOUT), D207.4 (DIN), D223.6 (BIN)
unnamed: D192.1 (VCC), R192.2
unnamed: D192.3 (DOUT), D208.4 (DIN), D224.6 (BIN)
unnamed: D193.1 (VCC), R193.2
unnamed: D193.3 (DOUT), D209.4 (DIN), D225.6 (BIN)
unnamed: D194.1 (VCC), R194.2
unnamed: D194.3 (DOUT), D210.4 (DIN), D226.6 (BIN)
unnamed: D195.1 (VCC), R195.2
unnamed: D195.3 (DOUT), D211.4 (DIN), D227.6 (BIN)
unnamed: D196.1 (VCC), R196.2
unnamed: D196.3 (DOUT), D212.4 (DIN), D228.6 (BIN)
unnamed: D197.1 (VCC), R197.2
unnamed: D197.3 (DOUT), D213.4 (DIN), D229.6 (BIN)
unnamed: D198.1 (VCC), R198.2
unnamed: D198.3 (DOUT), D214.4 (DIN), D230.6 (BIN)
unnamed: D199.1 (VCC), R199.2
unnamed: D199.3 (DOUT), D215.4 (DIN), D231.6 (BIN)
unnamed: D200.1 (VCC), R200.2
unnamed: D200.3 (DOUT), D216.4 (DIN), D232.6 (BIN)
unnamed: D201.1 (VCC), R201.2
unnamed: D201.3 (DOUT), D217.4 (DIN), D233.6 (BIN)
unnamed: D202.1 (VCC), R202.2
unnamed: D202.3 (DOUT), D218.4 (DIN), D234.6 (BIN)
unnamed: D203.1 (VCC), R203.2
unnamed: D203.3 (DOUT), D219.4 (DIN), D235.6 (BIN)
unnamed: D204.1 (VCC), R204.2
unnamed: D204.3 (DOUT), D220.4 (DIN), D236.6 (BIN)
unnamed: D205.1 (VCC), R205.2
unnamed: D205.3 (DOUT), D221.4 (DIN), D237.6 (BIN)
unnamed: D206.1 (VCC), R206.2
unnamed: D206.3 (DOUT), D222.4 (DIN), D238.6 (BIN)
unnamed: D207.1 (VCC), R207.2
unnamed: D207.3 (DOUT), D223.4 (DIN), D239.6 (BIN)
unnamed: D208.1 (VCC), R208.2
unnamed: D208.3 (DOUT), D224.4 (DIN), D240.6 (BIN)
unnamed: D209.1 (VCC), R209.2
unnamed: D209.3 (DOUT), D225.4 (DIN), D241.6 (BIN)
unnamed: D210.1 (VCC), R210.2
unnamed: D210.3 (DOUT), D226.4 (DIN), D242.6 (BIN)
unnamed: D211.1 (VCC), R211.2
unnamed: D211.3 (DOUT), D227.4 (DIN), D243.6 (BIN)
unnamed: D212.1 (VCC), R212.2
unnamed: D212.3 (DOUT), D228.4 (DIN), D244.6 (BIN)
unnamed: D213.1 (VCC), R213.2
unnamed: D213.3 (DOUT), D229.4 (DIN), D245.6 (BIN)
unnamed: D214.1 (VCC), R214.2
unnamed: D214.3 (DOUT), D230.4 (DIN), D246.6 (BIN)
unnamed: D215.1 (VCC), R215.2
unnamed: D215.3 (DOUT), D231.4 (DIN), D247.6 (BIN)
unnamed: D216.1 (VCC), R216.2
unnamed: D216.3 (DOUT), D232.4 (DIN), D248.6 (BIN)
unnamed: D217.1 (VCC), R217.2
unnamed: D217.3 (DOUT), D233.4 (DIN), D249.6 (BIN)
unnamed: D218.1 (VCC), R218.2
unnamed: D218.3 (DOUT), D234.4 (DIN), D250.6 (BIN)
unnamed: D219.1 (VCC), R219.2
unnamed: D219.3 (DOUT), D235.4 (DIN), D251.6 (BIN)
unnamed: D220.1 (VCC), R220.2
unnamed: D220.3 (DOUT), D236.4 (DIN), D252.6 (BIN)
unnamed: D221.1 (VCC), R221.2
unnamed: D221.3 (DOUT), D237.4 (DIN), D253.6 (BIN)
unnamed: D222.1 (VCC), R222.2
unnamed: D222.3 (DOUT), D238.4 (DIN), D254.6 (BIN)
unnamed: D223.1 (VCC), R223.2
unnamed: D223.3 (DOUT), D239.4 (DIN), D255.6 (BIN)
unnamed: D224.1 (VCC), R224.2
unnamed: D224.3 (DOUT), D240.4 (DIN), D256.6 (BIN)
unnamed: D225.1 (VCC), R225.2
unnamed: D226.1 (VCC), R226.2
unnamed: D3.6 (BIN), D226.3 (DOUT), D242.4 (DIN)
unnamed: D227.1 (VCC), R227.2
unnamed: D4.6 (BIN), D227.3 (DOUT), D243.4 (DIN)
unnamed: D228.1 (VCC), R228.2
unnamed: D5.6 (BIN), D228.3 (DOUT), D244.4 (DIN)
unnamed: D229.1 (VCC), R229.2
unnamed: D6.6 (BIN), D229.3 (DOUT), D245.4 (DIN)
unnamed: D230.1 (VCC), R230.2
unnamed: D7.6 (BIN), D230.3 (DOUT), D246.4 (DIN)
unnamed: D231.1 (VCC), R231.2
unnamed: D8.6 (BIN), D231.3 (DOUT), D247.4 (DIN)
unnamed: D232.1 (VCC), R232.2
unnamed: D9.6 (BIN), D232.3 (DOUT), D248.4 (DIN)
unnamed: D233.1 (VCC), R233.2
unnamed: D234.1 (VCC), R234.2
unnamed: D235.1 (VCC), R235.2
unnamed: D236.1 (VCC), R236.2
unnamed: D237.1 (VCC), R237.2
unnamed: D238.1 (VCC), R238.2
unnamed: D239.1 (VCC), R239.2
unnamed: D240.1 (VCC), R240.2
unnamed: D240.3 (DOUT), D256.4 (DIN)
unnamed: D241.1 (VCC), R241.2
unnamed: D242.1 (VCC), R242.2
unnamed: D243.1 (VCC), R243.2
unnamed: D244.1 (VCC), R244.2
unnamed: D245.1 (VCC), R245.2
unnamed: D246.1 (VCC), R246.2
unnamed: D247.1 (VCC), R247.2
unnamed: D248.1 (VCC), R248.2
unnamed: D9.4 (DIN), D25.6 (BIN), D248.3 (DOUT)
unnamed: D249.1 (VCC), R249.2
unnamed: D250.1 (VCC), R250.2
unnamed: D251.1 (VCC), R251.2
unnamed: D252.1 (VCC), R252.2
unnamed: D253.1 (VCC), R253.2
unnamed: D254.1 (VCC), R254.2
unnamed: D255.1 (VCC), R255.2
unnamed: D256.1 (VCC), R256.2
unnamed: D257.1 (K), R260.1
unnamed: D258.1 (K), R261.1
unnamed: D259.1 (K), R262.1

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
